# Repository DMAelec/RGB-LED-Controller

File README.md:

# RGB-LED-Controller
A PIC12F based high power RGB LED controller inspired from picprojects.org "Mood Light #101".
This version instead uses high power mosfets to control external LED's. Tested up to 3 Amps,
but can theoretically handle up to 5 Amps.
Firmware and schematic based from http://picprojects.org.uk/projects/rgb/index.htm
WORK IN PROGRESS

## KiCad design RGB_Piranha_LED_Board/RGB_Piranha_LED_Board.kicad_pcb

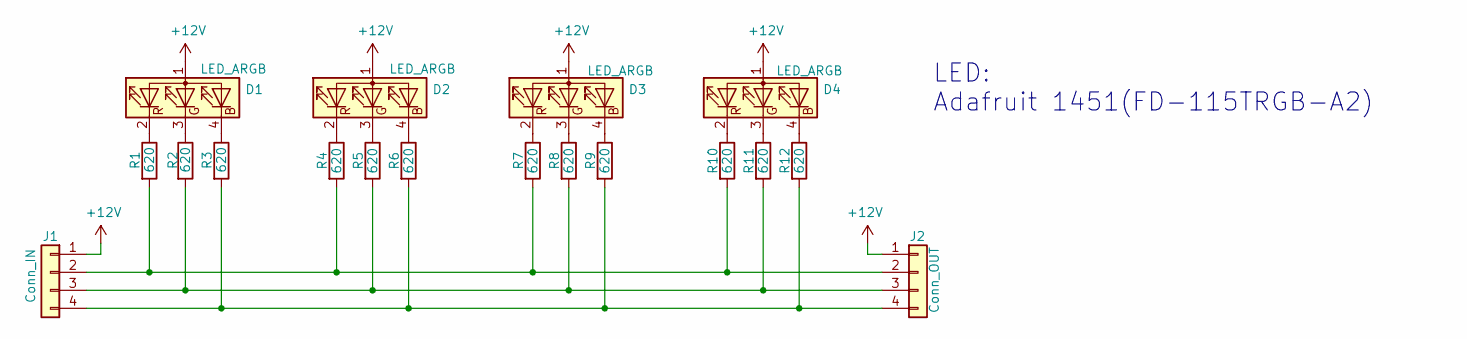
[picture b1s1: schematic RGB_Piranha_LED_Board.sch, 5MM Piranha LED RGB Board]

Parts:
D1, D2, D3, D4: LED_ARGB; LED_FD-115TRGB-A2
J1: Conn_IN; PinHeader_1x04_P2.54mm_Vertical
J2: Conn_OUT; PinSocket_1x04_P2.54mm_Vertical
R1, R2, R3, R4, R5, R6, R7, R8, R9, R10, R11, R12: 620; R_1210_3225Metric_Pad1.42x2.65mm_HandSolder

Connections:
+12V: D1.1 (A), D2.1 (A), D3.1 (A), D4.1 (A), J1.1, J2.1
unnamed: D1.2 (RK), R1.1
unnamed: D1.3 (GK), R2.1
unnamed: D1.4 (BK), R3.1
unnamed: D2.2 (RK), R4.1
unnamed: D2.3 (GK), R5.1
unnamed: D2.4 (BK), R6.1
unnamed: D3.2 (RK), R7.1
unnamed: D3.3 (GK), R8.1
unnamed: D3.4 (BK), R9.1
unnamed: D4.2 (RK), R10.1
unnamed: D4.3 (GK), R11.1
unnamed: D4.4 (BK), R12.1
unnamed: J1.2, J2.2, R1.2, R4.2, R7.2, R10.2
unnamed: J1.3, J2.3, R2.2, R5.2, R8.2, R11.2
unnamed: J1.4, J2.4, R3.2, R6.2, R9.2, R12.2

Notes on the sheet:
LED: Adafruit 1451(FD-115TRGB-A2)

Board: 2 copper layers, 18 parts (0 on the bottom side), 16 nets, no tracks yet.

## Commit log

2023-01-18 added readme
2023-02-12 Second Commit
2023-02-13 some changes
2023-02-13 some cleanup
2023-03-04 added custom footprint
2023-03-06 added custom LED footprint
2023-03-06 changed THT resistors to SMD
2023-03-06 added PDF schematic
2023-03-15 generated gerbers
